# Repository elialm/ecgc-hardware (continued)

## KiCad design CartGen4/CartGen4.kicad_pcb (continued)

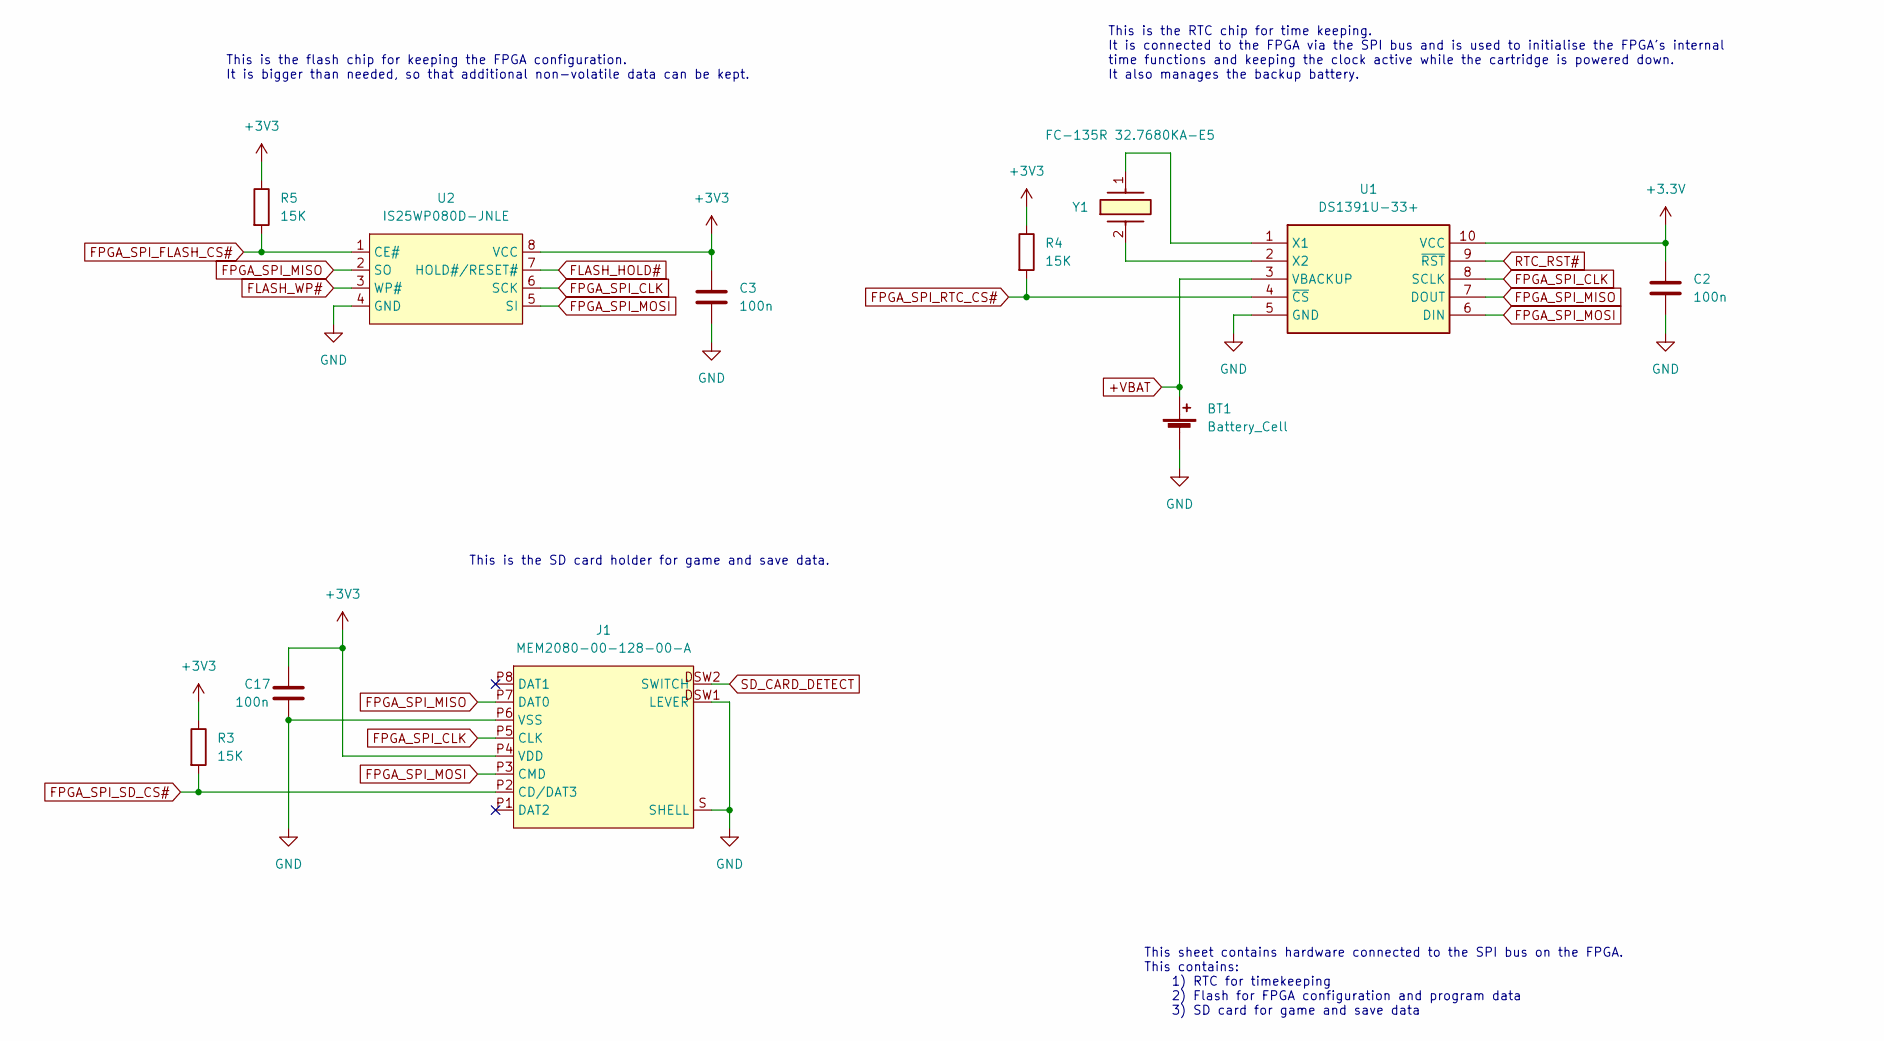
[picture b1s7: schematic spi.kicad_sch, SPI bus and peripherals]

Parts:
BT1: Battery_Cell; 2894
C2, C3, C17: 100n; C_0402_1005Metric_Pad0.74x0.62mm_HandSolder; Tolerance 20%; Voltage 3V3
J1: MEM2080-00-128-00-A
R3, R4, R5: 15K; R_0402_1005Metric_Pad0.72x0.64mm_HandSolder; Tolerance 10%
U1: DS1391U-33+; SOP50P490X110-10N
U2: IS25WP080D-JNLE; NE555DR
Y1: FC-135R 32.7680KA-E5; FC135R327680KAE3

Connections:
+VBAT: BT1.1 (+), U1.3 (VBACKUP)
FLASH_HOLD#: U2.7 (HOLD#/RESET#); also elsewhere on the board
FLASH_WP#: U2.3 (WP#); also elsewhere on the board
FPGA_SPI_CLK: J1.P5 (CLK), U1.8 (SCLK), U2.6 (SCK); also elsewhere on the board
FPGA_SPI_FLASH_CS#: R5.2, U2.1 (CE#); also elsewhere on the board
FPGA_SPI_MISO: J1.P7 (DAT0), U1.7 (DOUT), U2.2 (SO); also elsewhere on the board
FPGA_SPI_MOSI: J1.P3 (CMD), U1.6 (DIN), U2.5 (SI); also elsewhere on the board
FPGA_SPI_RTC_CS#: R4.2, U1.4 (~CS); also elsewhere on the board
FPGA_SPI_SD_CS#: J1.P2 (CD/DAT3), R3.2; also elsewhere on the board
GND: BT1.2 (-), C2.2, C3.2, C17.2, J1.DSW1 (LEVER), J1.P6 (VSS), J1.S (SHELL), U1.5 (GND), U2.4 (GND); also elsewhere on the board
unnamed: U1.1 (X1), Y1.1 (CRYSTAL)
unnamed: U1.2 (X2), Y1.2 (CRYSTAL)
RTC_RST#: U1.9 (~RST); also elsewhere on the board
SD_CARD_DETECT: J1.DSW2 (SWITCH); also elsewhere on the board

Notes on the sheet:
This is the RTC chip for time keeping. It is connected to the FPGA via the SPI bus and is used to initialise the FPGA's internal time functions and keeping the clock active while the cartridge is powered down. It also manages the backup battery.
This sheet contains hardware connected to the SPI bus on the FPGA. This contains: 1) RTC for timekeeping 2) Flash for FPGA configuration and program data 3) SD card for game and save data
This is the SD card holder for game and save data.
This is the flash chip for keeping the FPGA configuration. It is bigger than needed, so that additional non-volatile data can be kept.

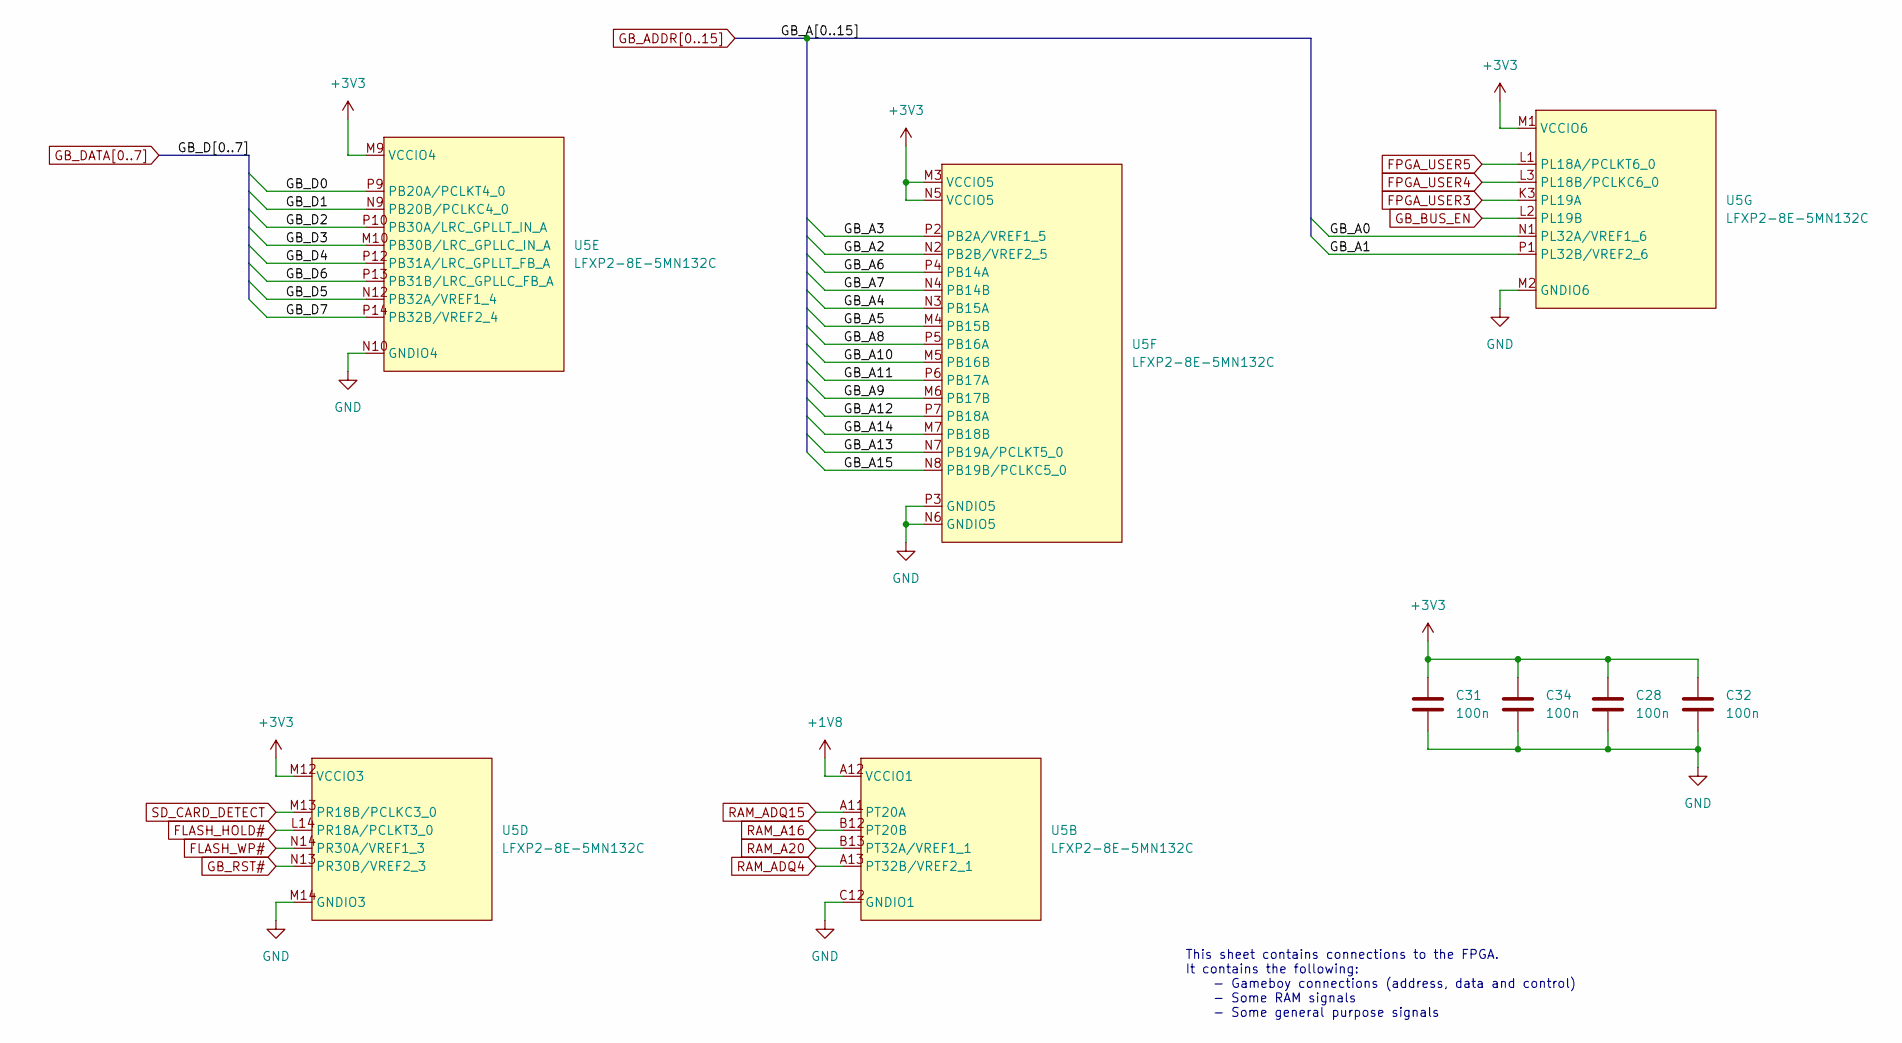
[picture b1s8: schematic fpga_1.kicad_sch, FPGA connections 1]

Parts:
C28, C31, C32, C34: 100n; C_0402_1005Metric_Pad0.74x0.62mm_HandSolder; Tolerance 20%; Voltage 3V3
U5: LFXP2-8E-5MN132C; BGA132C50P14X14_800X800X135

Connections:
+1V8: U5.A12 (VCCIO1); also elsewhere on the board
FLASH_HOLD#: U5.L14 (PR18A/PCLKT3_0); also elsewhere on the board
FLASH_WP#: U5.N14 (PR30A/VREF1_3); also elsewhere on the board
FPGA_USER3: U5.K3 (PL19A); also elsewhere on the board
FPGA_USER4: U5.L3 (PL18B/PCLKC6_0); also elsewhere on the board
FPGA_USER5: U5.L1 (PL18A/PCLKT6_0); also elsewhere on the board
GB_ADDR0: U5.N1 (PL32A/VREF1_6); also elsewhere on the board
GB_ADDR1: U5.P1 (PL32B/VREF2_6); also elsewhere on the board
GB_ADDR2: U5.N2 (PB2B/VREF2_5); also elsewhere on the board
GB_ADDR3: U5.P2 (PB2A/VREF1_5); also elsewhere on the board
GB_ADDR4: U5.N3 (PB15A); also elsewhere on the board
GB_ADDR5: U5.M4 (PB15B); also elsewhere on the board
GB_ADDR6: U5.P4 (PB14A); also elsewhere on the board
GB_ADDR7: U5.N4 (PB14B); also elsewhere on the board
GB_ADDR8: U5.P5 (PB16A); also elsewhere on the board
GB_ADDR9: U5.M6 (PB17B); also elsewhere on the board
GB_ADDR10: U5.M5 (PB16B); also elsewhere on the board
GB_ADDR11: U5.P6 (PB17A); also elsewhere on the board
GB_ADDR12: U5.P7 (PB18A); also elsewhere on the board
GB_ADDR13: U5.N7 (PB19A/PCLKT5_0); also elsewhere on the board
GB_ADDR14: U5.M7 (PB18B); also elsewhere on the board
GB_ADDR15: U5.N8 (PB19B/PCLKC5_0); also elsewhere on the board
GB_BUS_EN: U5.L2 (PL19B); also elsewhere on the board
GB_DATA0: U5.P9 (PB20A/PCLKT4_0); also elsewhere on the board
GB_DATA1: U5.N9 (PB20B/PCLKC4_0); also elsewhere on the board
GB_DATA2: U5.P10 (PB30A/LRC_GPLLT_IN_A); also elsewhere on the board
GB_DATA3: U5.M10 (PB30B/LRC_GPLLC_IN_A); also elsewhere on the board
GB_DATA4: U5.P12 (PB31A/LRC_GPLLT_FB_A); also elsewhere on the board
GB_DATA5: U5.N12 (PB32A/VREF1_4); also elsewhere on the board
GB_DATA6: U5.P13 (PB31B/LRC_GPLLC_FB_A); also elsewhere on the board
GB_DATA7: U5.P14 (PB32B/VREF2_4); also elsewhere on the board
GB_RST#: U5.N13 (PR30B/VREF2_3); also elsewhere on the board
GND: C28.2, C31.2, C32.2, C34.2, U5.C12 (GNDIO1), U5.M2 (GNDIO6), U5.M14 (GNDIO3), U5.N6 (GNDIO5), U5.N10 (GNDIO4), U5.P3 (GNDIO5); also elsewhere on the board
RAM_A16: U5.B12 (PT20B); also elsewhere on the board
RAM_A20: U5.B13 (PT32A/VREF1_1); also elsewhere on the board
RAM_ADQ4: U5.A13 (PT32B/VREF2_1); also elsewhere on the board
RAM_ADQ15: U5.A11 (PT20A); also elsewhere on the board
SD_CARD_DETECT: U5.M13 (PR18B/PCLKC3_0); also elsewhere on the board

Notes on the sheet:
This sheet contains connections to the FPGA. It contains the following: - Gameboy connections (address, data and control) - Some RAM signals - Some general purpose signals

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
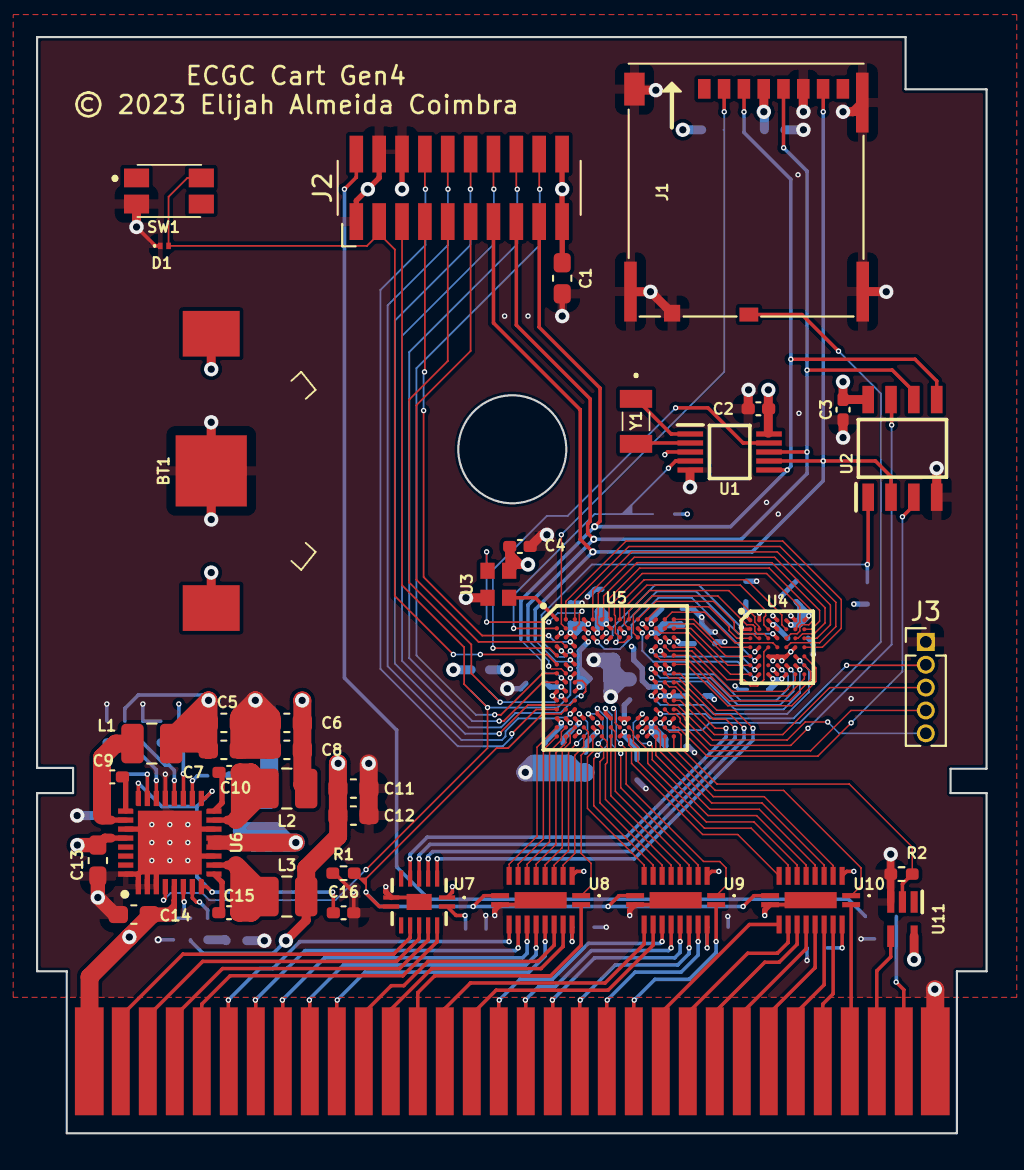
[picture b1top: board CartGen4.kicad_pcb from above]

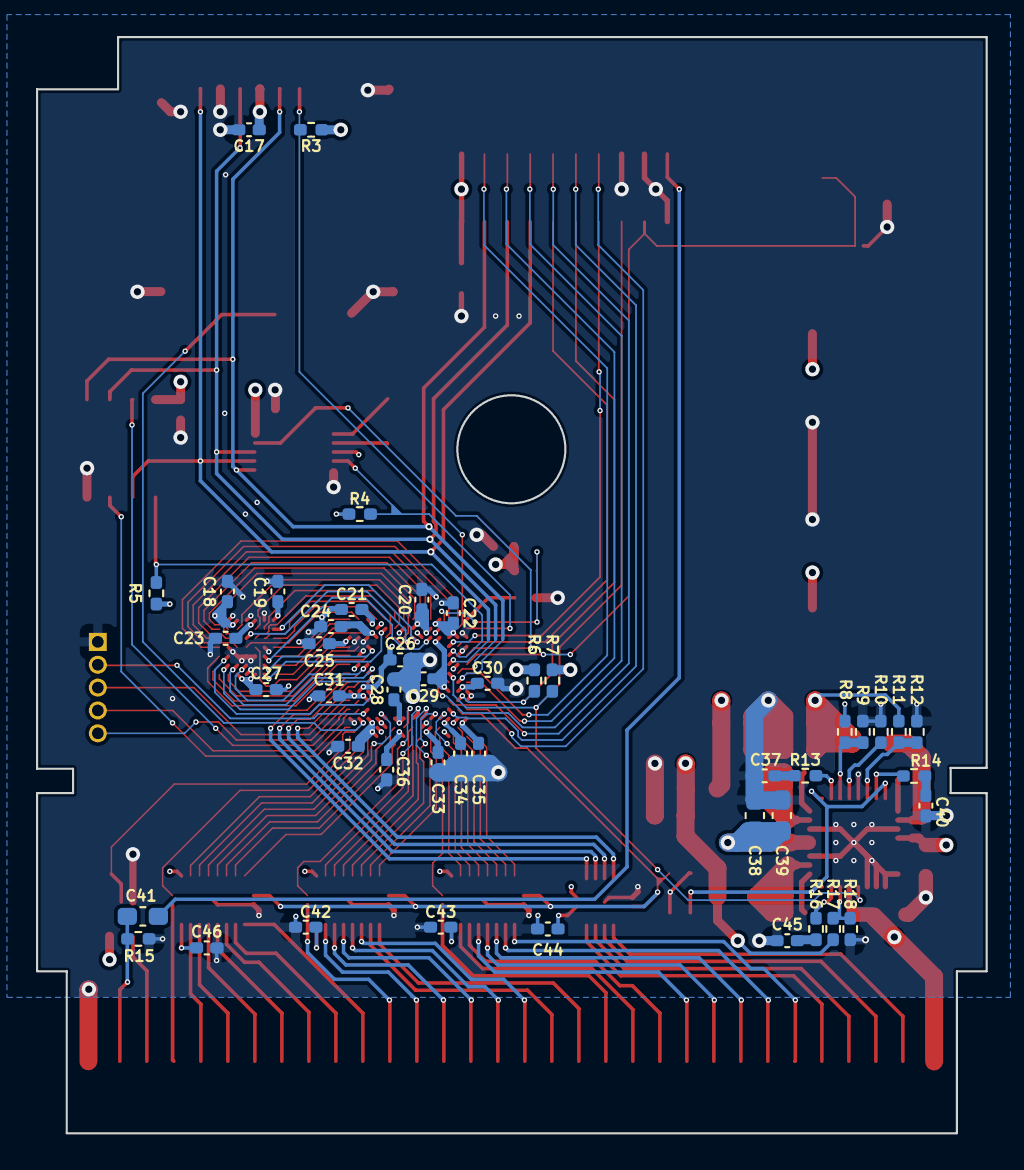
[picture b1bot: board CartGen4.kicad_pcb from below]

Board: 4 copper layers, 52.8 x 60.9 mm, 86 parts (46 on the bottom side), 145 nets.

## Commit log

2023-02-08 Included legacy documentation
2023-02-08 Added photo of prototype
2023-03-02 Added bypass capacitors to prototype
2023-04-06 Added audio schematic
2023-06-20 Added audio_mixer schematic
2023-09-22 Moved Gen3 to own directory
2023-09-22 Initial commit for Gen4
2023-09-22 Added FPGA and RAM symbols
2023-09-27 Added RAM and clock
2023-09-27 Added RTC + Changed clock IC
2023-09-28 Changed bus transceivers
2023-10-02 Added SPI flash
2023-10-02 Added SD card holder
2023-10-03 Changed control transceiver
2023-10-03 Added reset button
2023-10-03 Made part of FPGA connections
2023-10-04 Added FPGA <> Gameboy connections
2023-10-04 Connected and fixed reset
2023-10-04 Added copyright
2023-10-04 Added reference designators to everything
2023-10-04 Fixed DRC
2023-10-04 Cleaned up symbol fields
2023-10-05 Added symbol information to obvious stuff
2023-10-05 Added more symbol information
2023-10-05 Converted footprints
2023-10-05 Made and assigned clock footprint
2023-10-05 Added auto_saved_files to gitignore
2023-10-06 Assigned and made a few footprints
2023-10-06 Assigned all footprints
2023-10-06 Updated symbols
2023-10-06 Forgot to close footprint assignment tool
2023-10-06 Generated first PCB
2023-10-08 Made general component placement + fixed ADDR
2023-10-08 Fixed PS_PGOOD pullup
2023-10-08 Changed most R and C to 0402 size
2023-10-08 Made silkscreen smaller
2023-10-08 Wired power supply
2023-10-09 Implemented feedback from colleague
2023-10-09 Connected 5V side of level shifters
2023-10-10 Configured proper clearance for XP2
2023-10-10 Set same clearances on RAM
2023-10-10 Wired bus transceivers power
2023-10-10 Rearranged components
2023-10-10 Started routing FPGA
2023-10-10 Updated to adhere to JLCPCB capabilities
2023-10-10 Adjusted minimum via size
2023-10-10 Updated to the latest JLCPCB capabilities
2023-10-11 Started routing RAM
2023-10-13 Figured out how to run the DAMN ram traces
2023-10-13 Started routing more ram, but I'd better sleep...
2023-10-17 More RAM wire changes (i wanna cry)
2023-10-17 Wired all RAM signal wires (finally...)
2023-10-17 Adjusted RAM traces
2023-10-17 Connected bus transceivers
2023-10-17 Added RAM decoupling capacitors
2023-10-17 Connected FPGA ref clock
2023-10-19 Wired FPGA decoupling caps
2023-10-19 Planned rough location of SPI peripherals
2023-10-19 Reviewed cartridge edge clearances
2023-10-20 Chose battery retainer
2023-10-20 Wired SD power
2023-10-21 Added missing SPI CS
2023-10-21 Fanned out SPI bus
2023-10-24 Wired SPI bus
2023-10-24 Wired general purpose signals
2023-10-26 Wired 1V2 and 1V8 around FPGA and RAM
2023-10-26 Switched 1V2 and 1V8 supplies
2023-10-26 Wired all voltage rails
2023-10-27 Increased clearances between power planes
2023-10-30 Change JTAG pins to 1mm pitch
2023-10-31 Rerouted some RAM and GB CTRL traces
2023-10-31 Added external test header to schematic
2023-10-31 Added power source to J3 header
2023-10-31 Added J3 to PCB
2023-10-31 Flipped J2 to make pin 1 GND
2023-10-31 Added GB_AUDIO to expansion port
2023-10-31 Minor adjustments
2023-10-31 Switched from 1.00mm to 1.27mm pin headers
2023-11-01 Changed J3 to SMD header
2023-11-02 Routed expansion port
2023-11-02 Routed VBAT
2023-11-02 Increased clearances between GB lines
2023-11-02 Added bypass capacitors to transceivers
2023-11-02 Routed almost forgotten GB_BUS_EN
2023-11-02 Added decoupling capacitor to lone 1V8 pin
2023-11-02 Fixed clearance violations on power plane
2023-11-06 Changed GB_AUDIO location for better noise isolation
2023-11-06 Changed power pins to give the 3V3 rail 3A capabilities
2023-11-06 Added decoupling cap to expansion header to be sure
2023-11-07 Fixed GB_BUS_EN not being on 3V3 bank Added CLK_EN to ext clock
2023-11-17 Added © notice to PCB
2023-11-17 Added CERN-OHL-P license
2023-11-17 Updated field information
2023-11-17 Updated README with renders of Gen4
2023-11-17 Removed inline images since it was distracting
2023-11-17 Generated fabrication files for Gen4
2023-11-17 Fixed U10 excluded from F.Paste and F.Mask
2023-11-17 Updated some component fields
2023-11-17 Changed 50K size to 0603 due to unavailability
2023-11-17 Revert "Changed 50K size to 0603 due to unavailability"
    This reverts commit 7b462f06fc85ccc42ac1f7842e04da7b6c33922f.
2023-11-17 Added missing recommendations
2023-11-17 Forgot to update PCB
2023-11-20 Changed R19 to R13
2023-11-20 Reassigned RD geographically
2023-11-20 Minor fixes to reference designators
2023-11-20 Regenerated fabrication files
2024-01-09 Fixed silk screen placement Fixed RD misplacement Changed R16 supplier suggestion
2024-01-11 Removed fabrication files from version control
2024-02-25 Added improvement notes for documenting problems with current gen
2024-05-24 Added reference designator update to improvements
2024-10-06 Added recommendations
2026-03-13 Added improvements to programming pins
